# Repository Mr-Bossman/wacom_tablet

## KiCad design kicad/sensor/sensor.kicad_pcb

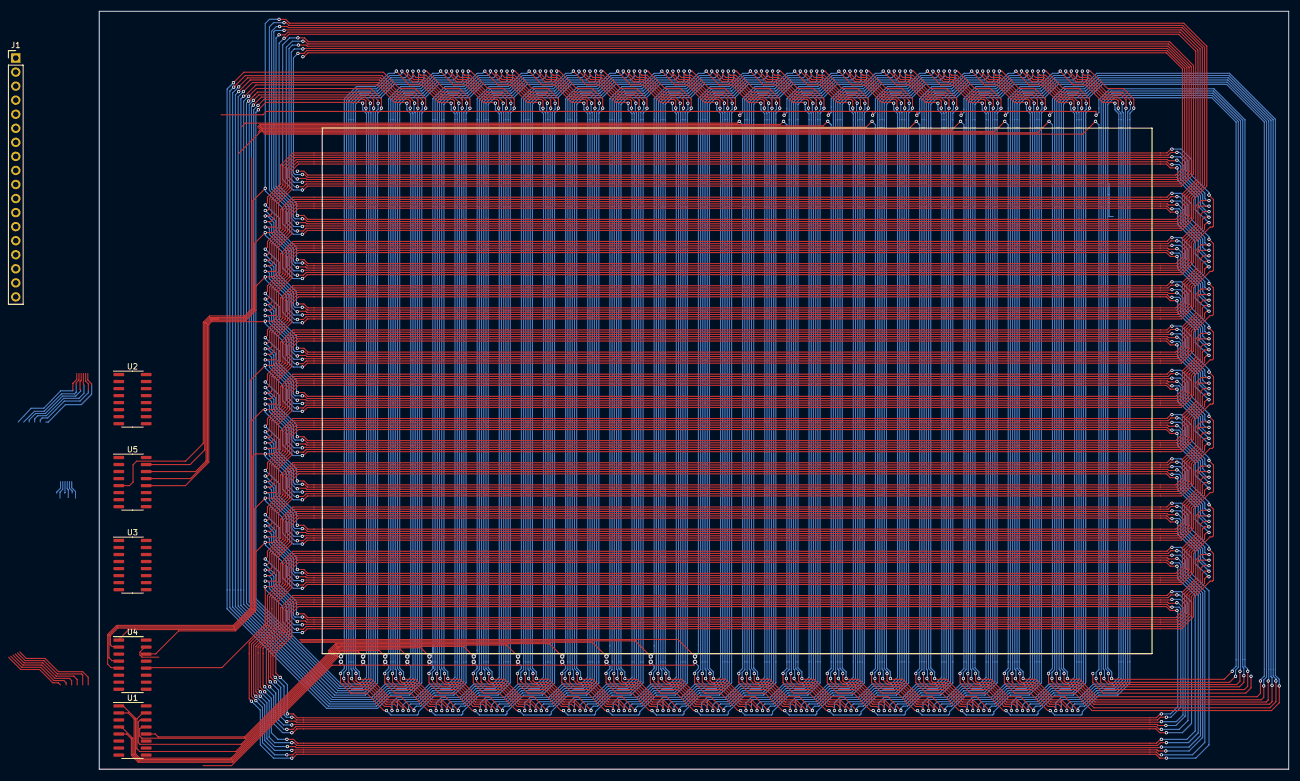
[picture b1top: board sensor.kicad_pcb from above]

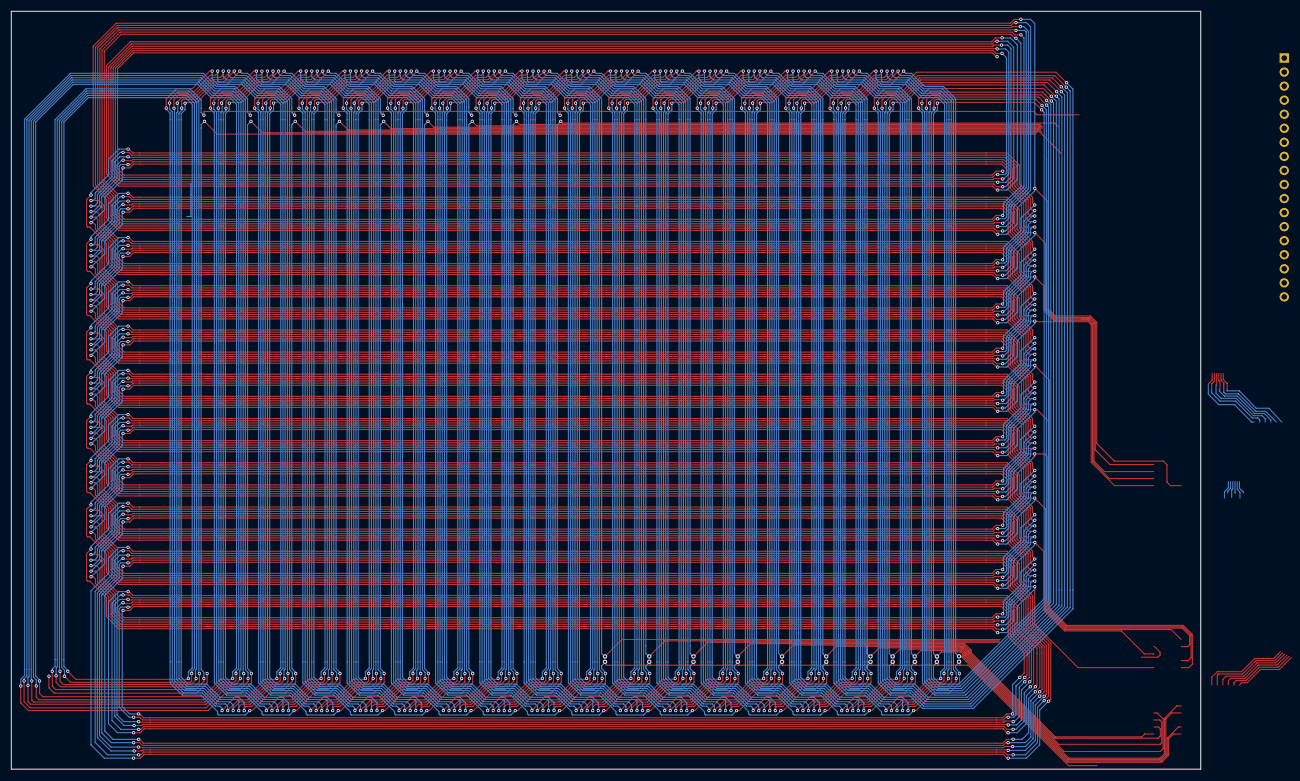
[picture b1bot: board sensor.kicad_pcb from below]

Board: 2 copper layers, 215.0 x 137.0 mm, 26 parts (10 on the bottom side), 33 nets.

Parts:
J1: CONN; PinHeader_1x18_P2.54mm_Vertical
U1: 150; SOIC-16_3.9x9.9mm_P1.27mm
U2: 152; SOIC-16_3.9x9.9mm_P1.27mm
U3: 153; SOIC-16_3.9x9.9mm_P1.27mm
U4: 156; SOIC-16_3.9x9.9mm_P1.27mm
U5: 155; SOIC-16_3.9x9.9mm_P1.27mm
U6, U7, U8, U9, U10, U11, U12, U13, U14, U15, U16, U17, U18, U19, U20, U21, U22, U23, U24, U25: jumper

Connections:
/150: J1.17, U1.6 (INH)
/152: J1.16, U2.6 (INH)
/153: J1.15, U3.6 (INH)
/155: J1.13, U5.6 (INH)
/156: J1.14, U4.6 (INH)
/A: J1.4, J1.5, U1.3 (X), U2.3 (X), U3.3 (X), U4.3 (X), U5.3 (X)
/P6: J1.6, U5.4 (X7)
/S0: J1.12, U1.11 (A), U2.11 (A), U3.11 (A), U4.11 (A), U5.11 (A)
/S1: J1.11, U1.10 (B), U2.10 (B), U3.10 (B), U4.10 (B), U5.10 (B)
/S2: J1.10, U1.9 (C), U2.9 (C), U3.9 (C), U4.9 (C), U5.9 (C)
/X0: U1.5 (X5), U11.1
/X1: U1.4 (X7), U13.1
/X2: U1.2 (X6), U12.1
/X3: U1.1 (X4), U10.1
/X4: U1.15 (X2), U8.1
/X5: U1.14 (X1), U7.1
/X6: U1.13 (X0), U6.1
/X7: U1.12 (X3), U9.1
/X8: U2.1 (X4), U18.1
/X9: U2.2 (X6), U20.1
/X10: U2.4 (X7), U21.1
/X11: U2.5 (X5), U19.1
/X12: U2.15 (X2), U16.1
/X13: U2.14 (X1), U15.1
/X14: U2.13 (X0), U14.1
/X15: U2.12 (X3), U17.1
/X16: U3.1 (X4), U22.1
/X17: U3.2 (X6), U24.1
/X18: U3.4 (X7), U25.1
/X19: U3.5 (X5), U23.1
GND: J1.1, J1.2, J1.3, U1.8 (VSS), U2.8 (VSS), U3.8 (VSS), U3.12 (X3), U3.13 (X0), U3.14 (X1), U3.15 (X2), U4.8 (VSS), U5.1 (X4), U5.2 (X6), U5.8 (VSS), U6.2, U7.2, U8.2, U9.2, U10.2, U11.2, U12.2, U13.2, U14.2, U15.2, U16.2, U17.2, U18.2, U19.2, U20.2, U21.2, U22.2, U23.2, U24.2, U25.2
VDD: J1.7, J1.8, U1.16 (VDD), U2.16 (VDD), U3.16 (VDD), U4.16 (VDD), U5.16 (VDD)
VSS: J1.9, U1.7 (VEE), U2.7 (VEE), U3.7 (VEE), U4.7 (VEE), U5.7 (VEE)

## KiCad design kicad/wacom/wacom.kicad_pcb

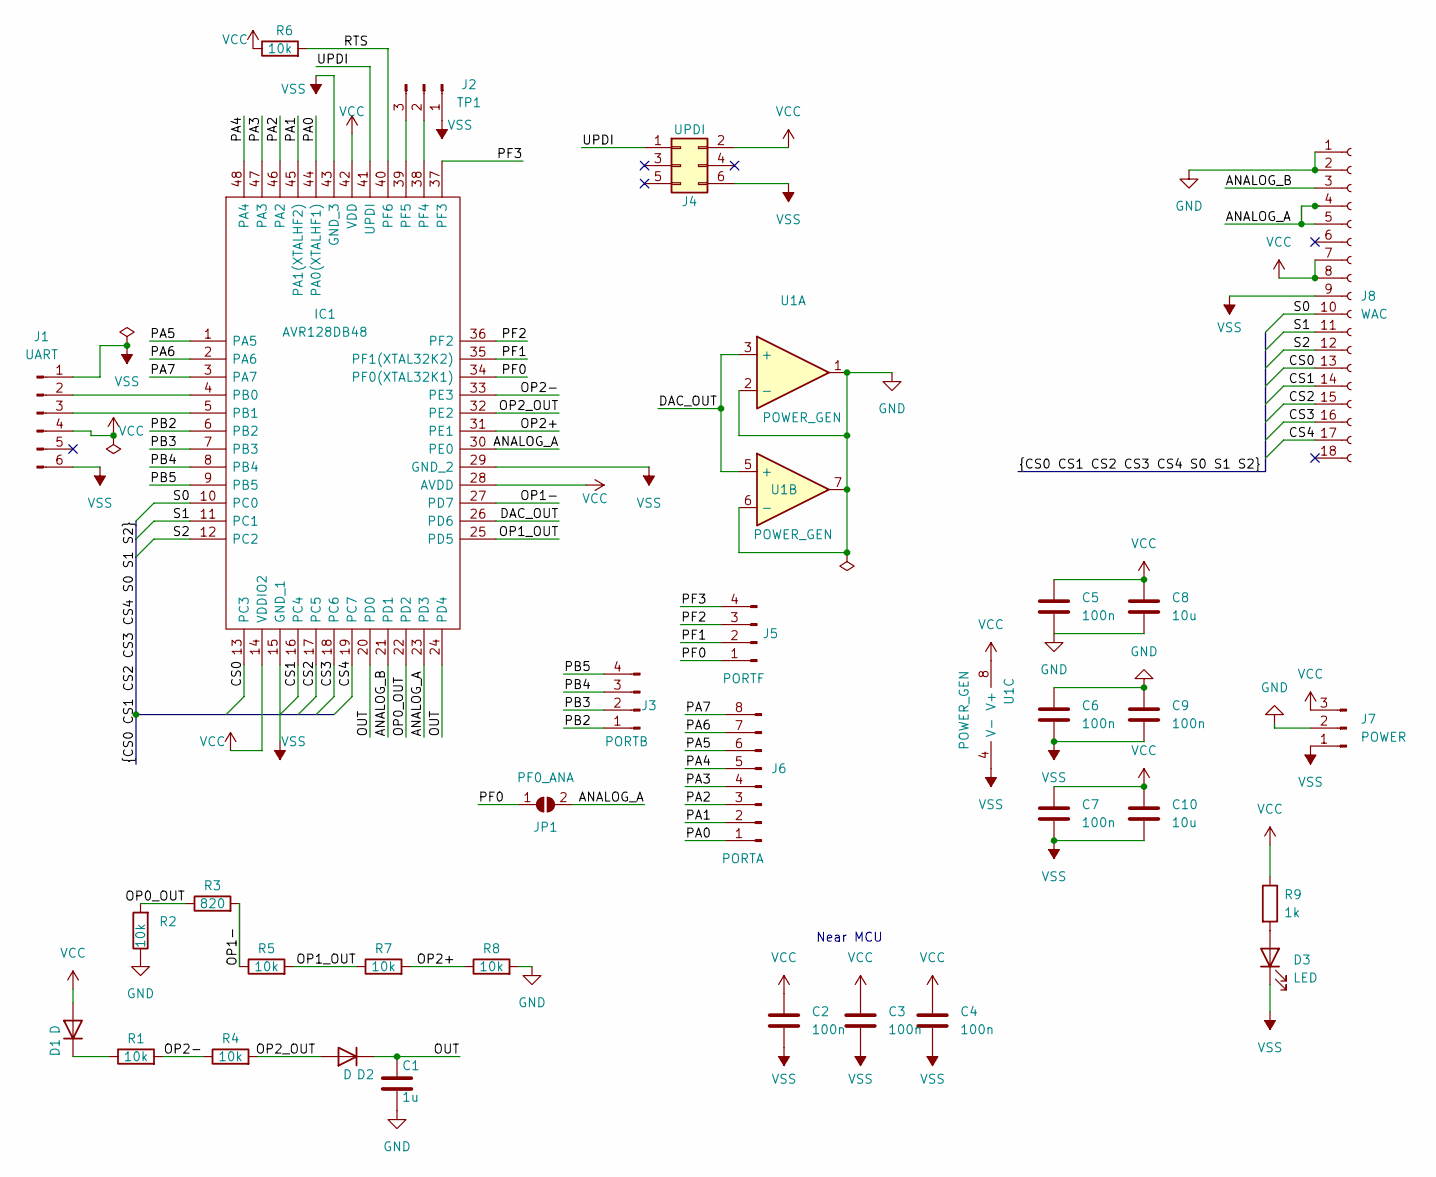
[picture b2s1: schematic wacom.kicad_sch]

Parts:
C1: 1u; C_0603_1608Metric_Pad1.08x0.95mm_HandSolder
C2, C3, C4, C5, C6, C7, C9: 100n; C_0603_1608Metric_Pad1.08x0.95mm_HandSolder
C8, C10: 10u; C_0603_1608Metric_Pad1.08x0.95mm_HandSolder
D1, D2: D; D_SOD-323_HandSoldering
D3: LED; LED_0603_1608Metric_Pad1.05x0.95mm_HandSolder
IC1: AVR128DB48; QFP50P900X900X120-48N; Manufacturer_Part_Number AVR128DB48-I/PT; Mouser Part Number 579-AVR128DB48-I/PT
J1: UART; PinHeader_1x06_P2.54mm_Vertical
J2: TP1; PinHeader_1x03_P2.54mm_Vertical
J3: PORTB; PinHeader_1x04_P2.54mm_Vertical
J4: UPDI; PinHeader_2x03_P2.54mm_Vertical
J5: PORTF; PinHeader_1x04_P2.54mm_Vertical
J6: PORTA; PinHeader_1x08_P2.54mm_Vertical
J7: POWER; PinHeader_1x03_P2.54mm_Vertical
J8: WAC; PinSocket_2x09_P2.54mm_Vertical
JP1: PF0_ANA; SolderJumper-2_P1.3mm_Open_RoundedPad1.0x1.5mm
R1, R2, R4, R5, R6, R7, R8: 10k; R_0603_1608Metric_Pad0.98x0.95mm_HandSolder
R3: 820; R_0603_1608Metric_Pad0.98x0.95mm_HandSolder
R9: 1k; R_0603_1608Metric_Pad0.98x0.95mm_HandSolder
U1: POWER_GEN; SOIC-8_3.9x4.9mm_P1.27mm

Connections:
/ANALOG_A: IC1.23 (PD3), IC1.30 (PE0), J8.4, J8.5, JP1.2 (B)
/ANALOG_B: IC1.21 (PD1), J8.3
/CS0: IC1.13 (PC3), J8.13
/CS1: IC1.16 (PC4), J8.14
/CS2: IC1.17 (PC5), J8.15
/CS3: IC1.18 (PC6), J8.16
/CS4: IC1.19 (PC7), J8.17
/DAC_OUT: IC1.26 (PD6), U1.3 (+), U1.5 (+)
/OP0_OUT: IC1.22 (PD2), R2.2, R3.1
/OP1-: IC1.27 (PD7), R3.2, R5.1
/OP1_OUT: IC1.25 (PD5), R5.2, R7.1
/OP2+: IC1.31 (PE1), R7.2, R8.1
/OP2-: IC1.33 (PE3), R1.2, R4.1
/OP2_OUT: D2.2 (A), IC1.32 (PE2), R4.2
/OUT: C1.1, D2.1 (K), IC1.20 (PD0), IC1.24 (PD4)
/PA0: IC1.44 (PA0(XTALHF1)), J6.1
/PA1: IC1.45 (PA1(XTALHF2)), J6.2
/PA2: IC1.46 (PA2), J6.3
/PA3: IC1.47 (PA3), J6.4
/PA4: IC1.48 (PA4), J6.5
/PA5: IC1.1 (PA5), J6.6
/PA6: IC1.2 (PA6), J6.7
/PA7: IC1.3 (PA7), J6.8
/PB2: IC1.6 (PB2), J3.1
/PB3: IC1.7 (PB3), J3.2
/PB4: IC1.8 (PB4), J3.3
/PB5: IC1.9 (PB5), J3.4
/PF0: IC1.34 (PF0(XTAL32K1)), J5.1, JP1.1 (A)
/PF1: IC1.35 (PF1(XTAL32K2)), J5.2
/PF2: IC1.36 (PF2), J5.3
/PF3: IC1.37 (PF3), J5.4
/RTS: IC1.40 (PF6), R6.2
/S0: IC1.10 (PC0), J8.10
/S1: IC1.11 (PC1), J8.11
/S2: IC1.12 (PC2), J8.12
/UPDI: IC1.41 (UPDI), J4.1
GND: C1.2, C5.2, C6.1, C8.2, C9.1, J7.2, J8.1, J8.2, R2.1, R8.2, U1.1, U1.2 (-), U1.6 (-), U1.7
unnamed: D1.1 (K), R1.1
unnamed: D3.2 (A), R9.2
unnamed: IC1.4 (PB0), J1.2
unnamed: IC1.5 (PB1), J1.3
unnamed: IC1.38 (PF4), J2.2
unnamed: IC1.39 (PF5), J2.3
VCC: C2.1, C3.1, C4.1, C5.1, C7.1, C8.1, C10.1, D1.2 (A), IC1.14 (VDDIO2), IC1.28 (AVDD), IC1.42 (VDD), J1.4, J4.2, J7.3, J8.7, J8.8, R6.1, R9.1, U1.8 (V+)
VSS: C2.2, C3.2, C4.2, C6.2, C7.2, C9.2, C10.2, D3.1 (K), IC1.15 (GND_1), IC1.29 (GND_2), IC1.43 (GND_3), J1.1, J1.6, J2.1, J4.6, J7.1, J8.9, U1.4 (V-)

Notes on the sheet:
Near MCU

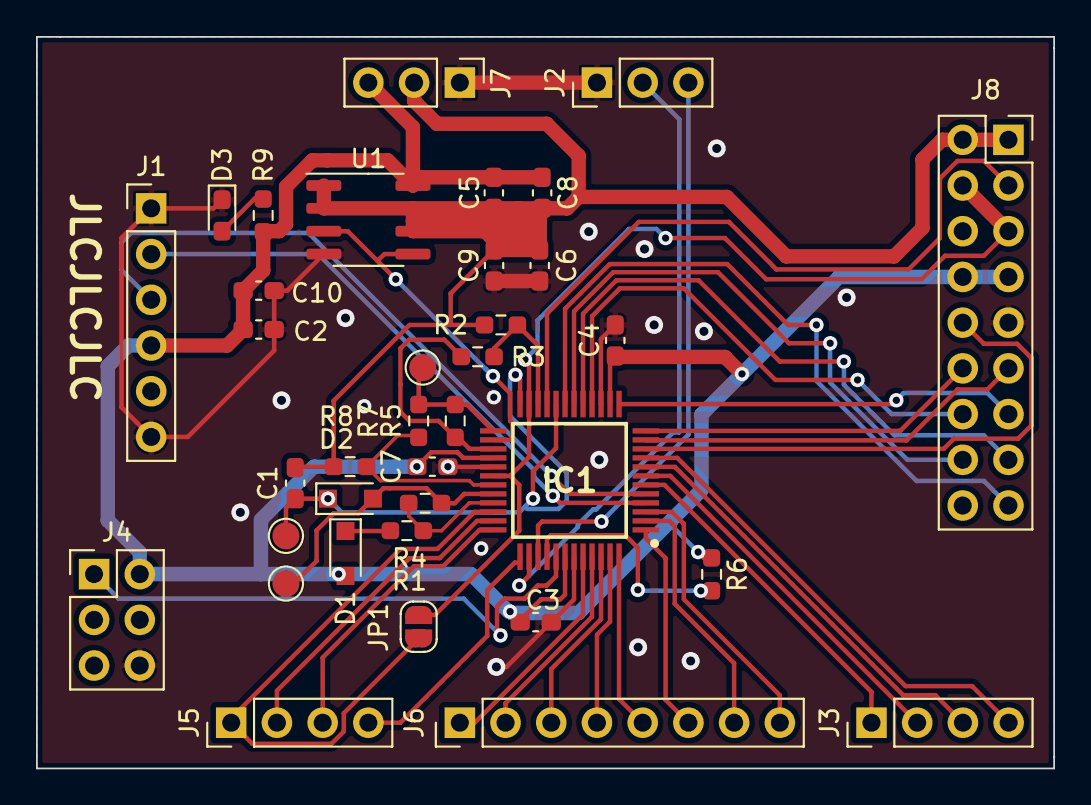
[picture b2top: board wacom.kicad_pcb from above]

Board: 2 copper layers, 56.5 x 40.6 mm, 33 parts (0 on the bottom side), 45 nets.

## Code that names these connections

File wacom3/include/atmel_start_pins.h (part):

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
#include <port.h>
/**
 * \brief Set PA0 pull mode
 *
 * Configure pin to pull up, down or disable pull mode, supported pull
 * modes are defined by device used
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}

/**
 * \brief Set PA0 data direction
 *
 * Select if the pin data direction is input, output or disabled.
 * If disabled state is not possible, this function throws an assert.
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}

/**
 * \brief Set PA0 input/sense configuration
 *
 * Enable/disable PA0 digital input buffer and pin change interrupt,
 * select pin interrupt edge/level sensing mode
 *
 * \param[in] isc PORT_ISC_INTDISABLE_gc    = Iterrupt disabled but input buffer enabled
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}

/**
 * \brief Set PA0 inverted mode
 *
 * Enable or disable inverted I/O on a pin
 *
 * \param[in] inverted true  = I/O on PA0 is inverted
 *                     false = I/O on PA0 is not inverted
 */
static inline void PA0_set_inverted(const bool inverted)
{
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}

/**
 * \brief Set PA0 level
 *
 * Sets output level on a pin
 *
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}

/**
 * \brief Toggle output level on PA0
 *
 * Toggle the pin level
 */
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}

/**
 * \brief Get level on PA0
 *
 * Reads the level on a pin
 */
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}

/**
 * \brief Set PA1 pull mode
 *
 * Configure pin to pull up, down or disable pull mode, supported pull
 * modes are defined by device used
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}

/**
 * \brief Set PA1 data direction
 *
 * Select if the pin data direction is input, output or disabled.
 * If disabled state is not possible, this function throws an assert.
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}

/**
 * \brief Set PA1 input/sense configuration
 *
 * Enable/disable PA1 digital input buffer and pin change interrupt,
 * select pin interrupt edge/level sensing mode
 *
 * \param[in] isc PORT_ISC_INTDISABLE_gc    = Iterrupt disabled but input buffer enabled
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}

/**
 * \brief Set PA1 inverted mode
 *
 * Enable or disable inverted I/O on a pin
 *
 * \param[in] inverted true  = I/O on PA1 is inverted
 *                     false = I/O on PA1 is not inverted
 */
static inline void PA1_set_inverted(const bool inverted)
{
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}

/**
 * \brief Set PA1 level
 *
 * Sets output level on a pin
 *
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}

/**
 * \brief Toggle output level on PA1
 *
 * Toggle the pin level
 */
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}

/**
 * \brief Get level on PA1
 *
 * Reads the level on a pin
 */
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	return PORTA_get_pin_level(1);
}
/**
 * \brief Set PD2 pull mode
 *
 * Configure pin to pull up, down or disable pull mode, supported pull
 * modes are defined by device used
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}

/**
 * \brief Set PD2 data direction
 *
 * Select if the pin data direction is input, output or disabled.
 * If disabled state is not possible, this function throws an assert.
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}

/**
 * \brief Set PD2 input/sense configuration
 *
 * Enable/disable PD2 digital input buffer and pin change interrupt,
 * select pin interrupt edge/level sensing mode
 *
 * \param[in] isc PORT_ISC_INTDISABLE_gc    = Iterrupt disabled but input buffer enabled
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}

/**
 * \brief Set PD2 inverted mode
 *
 * Enable or disable inverted I/O on a pin
 *
 * \param[in] inverted true  = I/O on PD2 is inverted
 *                     false = I/O on PD2 is not inverted
 */
static inline void PD2_set_inverted(const bool inverted)
{
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}

/**
 * \brief Set PD2 level
 *
 * Sets output level on a pin
 *
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}

/**
 * \brief Toggle output level on PD2
 *
 * Toggle the pin level
 */
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}

/**
 * \brief Get level on PD2
 *
 * Reads the level on a pin
 */
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}

/**
 * \brief Set PD3 pull mode
 *
 * Configure pin to pull up, down or disable pull mode, supported pull
 * modes are defined by device used
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}

/**
 * \brief Set PD3 data direction
 *
 * Select if the pin data direction is input, output or disabled.
 * If disabled state is not possible, this function throws an assert.
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}

/**
 * \brief Set PD3 input/sense configuration
 *
 * Enable/disable PD3 digital input buffer and pin change interrupt,
 * select pin interrupt edge/level sensing mode
 *
 * \param[in] isc PORT_ISC_INTDISABLE_gc    = Iterrupt disabled but input buffer enabled
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}

/**
 * \brief Set PD3 inverted mode
 *
 * Enable or disable inverted I/O on a pin
 *
 * \param[in] inverted true  = I/O on PD3 is inverted
 *                     false = I/O on PD3 is not inverted
 */
static inline void PD3_set_inverted(const bool inverted)
{
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}

/**
 * \brief Set PD3 level
 *
 * Sets output level on a pin
 *
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}

/**
 * \brief Toggle output level on PD3
 *
 * Toggle the pin level
 */
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}

/**
 * \brief Get level on PD3
 *
 * Reads the level on a pin
 */
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}

/**
 * \brief Set PD5 pull mode
 *
 * Configure pin to pull up, down or disable pull mode, supported pull
 * modes are defined by device used
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}

/**
 * \brief Set PD5 data direction
 *
 * Select if the pin data direction is input, output or disabled.
 * If disabled state is not possible, this function throws an assert.
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}

/**
 * \brief Set PD5 input/sense configuration
 *
 * Enable/disable PD5 digital input buffer and pin change interrupt,
 * select pin interrupt edge/level sensing mode
 *
 * \param[in] isc PORT_ISC_INTDISABLE_gc    = Iterrupt disabled but input buffer enabled
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}

/**
 * \brief Set PD5 inverted mode
 *
 * Enable or disable inverted I/O on a pin
 *
 * \param[in] inverted true  = I/O on PD5 is inverted
 *                     false = I/O on PD5 is not inverted
 */
static inline void PD5_set_inverted(const bool inverted)
{
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}

/**
 * \brief Set PD5 level
 *
 * Sets output level on a pin
 *
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}

/**
 * \brief Toggle output level on PD5
 *
 * Toggle the pin level
 */
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}

/**
 * \brief Get level on PD5
 *
 * Reads the level on a pin
 */
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}

/**
 * \brief Set PD7 pull mode
 *
 * Configure pin to pull up, down or disable pull mode, supported pull
 * modes are defined by device used
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}

/**
 * \brief Set PD7 data direction
 *
 * Select if the pin data direction is input, output or disabled.
 * If disabled state is not possible, this function throws an assert.
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}

/**
 * \brief Set PD7 input/sense configuration
 *
 * Enable/disable PD7 digital input buffer and pin change interrupt,
 * select pin interrupt edge/level sensing mode
 *
 * \param[in] isc PORT_ISC_INTDISABLE_gc    = Iterrupt disabled but input buffer enabled
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}

/**
 * \brief Set PD7 inverted mode
 *
 * Enable or disable inverted I/O on a pin
 *
 * \param[in] inverted true  = I/O on PD7 is inverted
 *                     false = I/O on PD7 is not inverted
 */
static inline void PD7_set_inverted(const bool inverted)
{
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}

/**
 * \brief Set PD7 level
 *
 * Sets output level on a pin
 *
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}

/**
 * \brief Toggle output level on PD7
 *
 * Toggle the pin level
 */
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}

/**
 * \brief Get level on PD7
 *
 * Reads the level on a pin
 */
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}

/**
 * \brief Set PE0 pull mode
 *
 * Configure pin to pull up, down or disable pull mode, supported pull
 * modes are defined by device used
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}

/**
 * \brief Set PE0 data direction
 *
 * Select if the pin data direction is input, output or disabled.
 * If disabled state is not possible, this function throws an assert.
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}

/**
 * \brief Set PE0 input/sense configuration
 *
 * Enable/disable PE0 digital input buffer and pin change interrupt,
 * select pin interrupt edge/level sensing mode
 *
 * \param[in] isc PORT_ISC_INTDISABLE_gc    = Iterrupt disabled but input buffer enabled
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}

/**
 * \brief Set PE0 inverted mode
 *
 * Enable or disable inverted I/O on a pin
 *
 * \param[in] inverted true  = I/O on PE0 is inverted
 *                     false = I/O on PE0 is not inverted
 */
static inline void PE0_set_inverted(const bool inverted)
{
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}

/**
 * \brief Set PE0 level
 *
 * Sets output level on a pin
 *
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}

/**
 * \brief Toggle output level on PE0
 *
 * Toggle the pin level
 */
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}

/**
 * \brief Get level on PE0
 *
 * Reads the level on a pin
 */
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}

/**
 * \brief Set PE1 pull mode
 *
 * Configure pin to pull up, down or disable pull mode, supported pull
 * modes are defined by device used
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}

/**
 * \brief Set PE1 data direction
 *
 * Select if the pin data direction is input, output or disabled.
 * If disabled state is not possible, this function throws an assert.
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}

/**
 * \brief Set PE1 input/sense configuration
 *
 * Enable/disable PE1 digital input buffer and pin change interrupt,
 * select pin interrupt edge/level sensing mode
 *
 * \param[in] isc PORT_ISC_INTDISABLE_gc    = Iterrupt disabled but input buffer enabled
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}

/**
 * \brief Set PE1 inverted mode
 *
 * Enable or disable inverted I/O on a pin
 *
 * \param[in] inverted true  = I/O on PE1 is inverted
 *                     false = I/O on PE1 is not inverted
 */
static inline void PE1_set_inverted(const bool inverted)
{
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}

/**
 * \brief Set PE1 level
 *
 * Sets output level on a pin
 *
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}

/**
 * \brief Toggle output level on PE1
 *
 * Toggle the pin level
 */
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}

/**
 * \brief Get level on PE1
 *
 * Reads the level on a pin
 */
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}

/**
 * \brief Set PE2 pull mode
 *
 * Configure pin to pull up, down or disable pull mode, supported pull
 * modes are defined by device used
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}

/**
 * \brief Set PE2 data direction
 *
 * Select if the pin data direction is input, output or disabled.
 * If disabled state is not possible, this function throws an assert.
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}

/**
 * \brief Set PE2 input/sense configuration
 *
 * Enable/disable PE2 digital input buffer and pin change interrupt,
 * select pin interrupt edge/level sensing mode
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
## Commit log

2022-05-06 init
2022-05-08 add inds
2022-05-08 works
2022-05-08 kicad
2022-05-08 python view
2022-05-09 python
2022-05-10 images and python
2022-05-10 add sensor sch
2022-05-25 add kicad plugin
2022-05-27 auto update
2022-05-27 update auto script
2022-05-27 script update
